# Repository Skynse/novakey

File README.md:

# NovaKey

An open-source 16-key macropad with three rotary encoders, custom firmware, and a companion configuration app.

## Novakey studio

Studio is the desktop app for the novakey. It can be used to configure profiles and keybinds

## Hardware

The PCB was designed in KiCad. Source files are in `kicad_files/`.

<table>
  <tr>
    <td align="center"><br><sub>Top</sub></td>
    <td align="center"><br><sub>Bottom</sub></td>
  </tr>
</table>

<details>
<summary>Schematic</summary>

</details>

## Bill of materials

### Electronics

| Ref | Qty | Part | Footprint / notes |
| --- | --- | --- | --- |
| A1 | 1 | Raspberry Pi Pico | Through-hole ([datasheet](https://datasheets.raspberrypi.com/pico/pico-datasheet.pdf)) |
| U2 | 1 | 0.91" 128x32 I2C OLED (ER-OLEDM0.91-1) | I2C ([datasheet](https://www.buydisplay.com/download/manual/ER-OLEDM0.91-1_Datasheet.pdf)) |
| SW1–SW3 | 3 | EC11 rotary encoder with push switch | Alps EC11E, vertical, 20 mm shaft |
| SW4–SW19 | 16 | Kailh MX hotswap socket | MX 1.00u |
| D1–D16 | 16 | Signal diode (e.g. 1N4148) | DO-35 through-hole, 7.62 mm pitch |
| — | 1 | NovaKey PCB | Gerbers in `pcbway_production/` |

### Mechanical

| Qty | Part | Source |
| --- | --- | --- |
| 16 | MX-style switches | Any MX-compatible switch |
| 16 | 1u keycaps | Any MX-compatible keycaps |
| 3 | Encoder knobs | 3D printed, `CAD/Knob.FCStd` |
| 1 | Enclosure base | 3D printed, `CAD/enclosure_v3/Base_flat.stl` |
| 1 | Enclosure top | 3D printed, `CAD/enclosure_v3/Upper_flat_base.stl` |

The KiCad-exported BOM is in `kicad_files/bill_of_materials.csv`.

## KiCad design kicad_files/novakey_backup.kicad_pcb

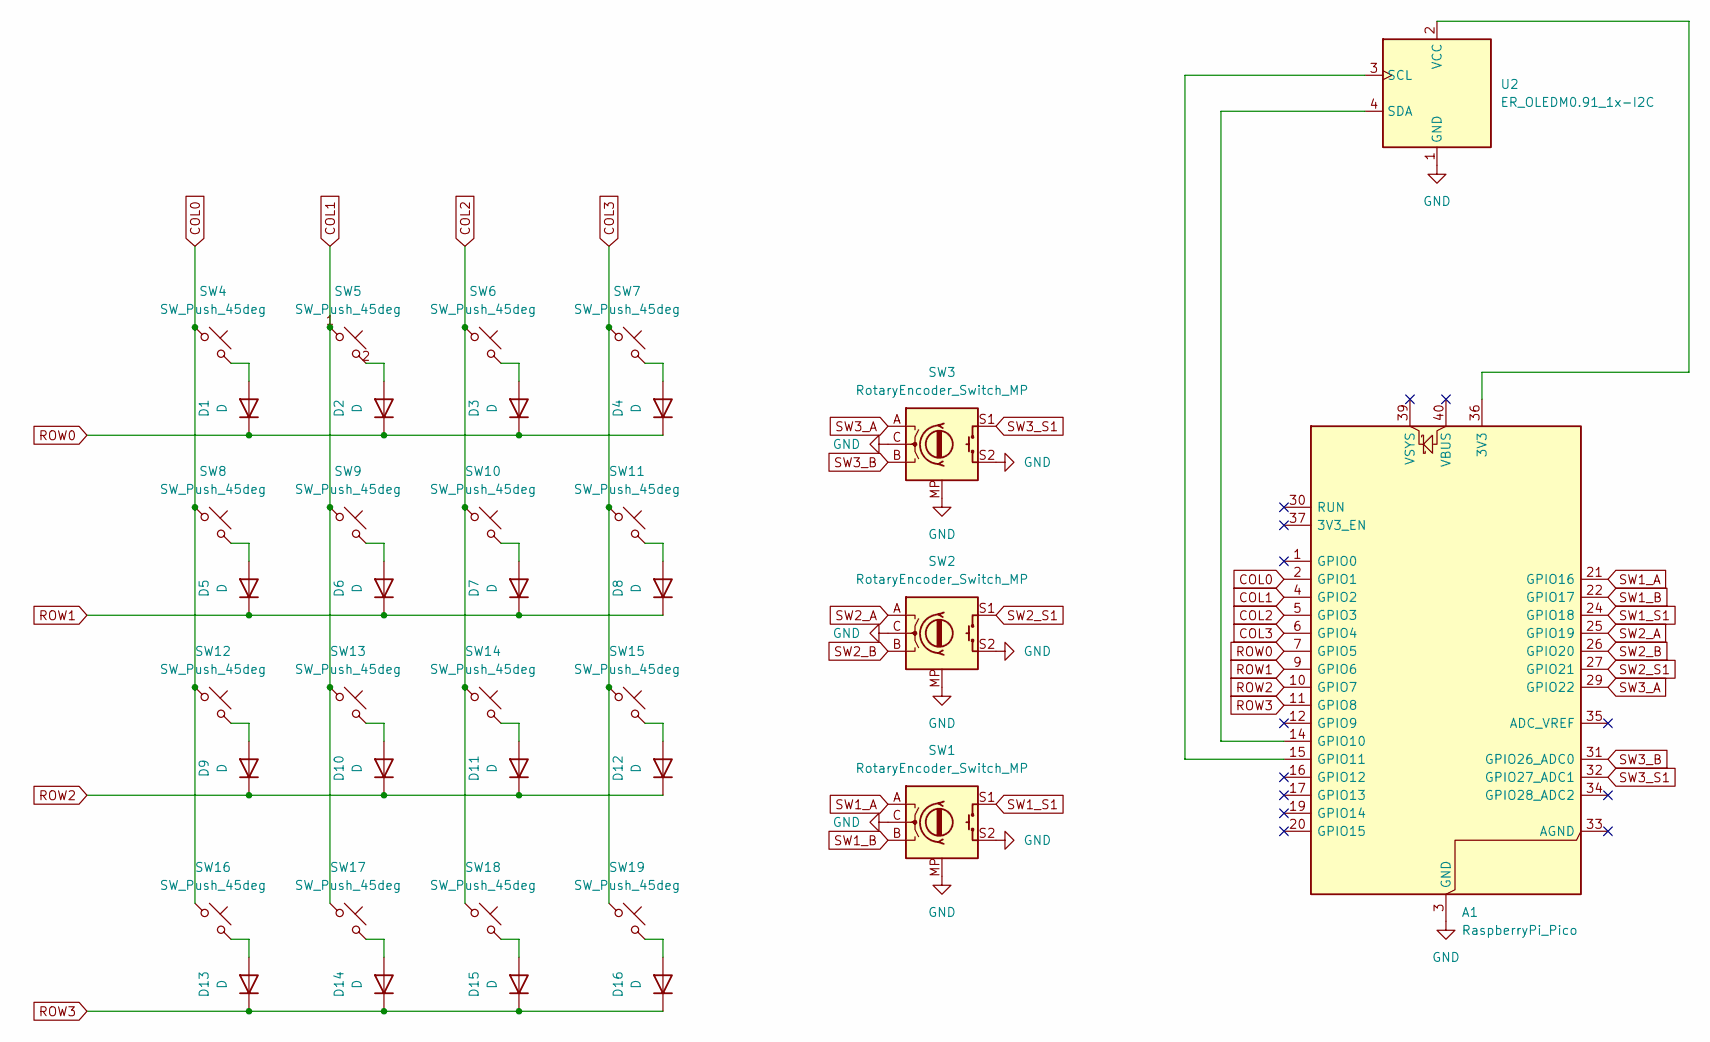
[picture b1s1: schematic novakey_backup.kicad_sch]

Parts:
A1: RaspberryPi_Pico; RaspberryPi_Pico_Common_THT
D1, D2, D3, D4, D5, D6, D7, D8, D9, D10, D11, D12, D13, D14, D15, D16: D; D_DO-35_SOD27_P7.62mm_Horizontal
SW1, SW2, SW3: RotaryEncoder_Switch_MP; RotaryEncoder_Alps_EC11E-Switch_Vertical_H20mm
SW4, SW5, SW6, SW7, SW8, SW9, SW10, SW11, SW12, SW13, SW14, SW15, SW16, SW17, SW18, SW19: SW_Push_45deg; SW_Hotswap_Kailh_MX_1.00u
U2: ER_OLEDM0.91_1x-I2C

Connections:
COL0: A1.2 (GPIO1), SW4.1, SW8.1, SW12.1, SW16.1
COL1: A1.4 (GPIO2), SW5.1, SW9.1, SW13.1, SW17.1
COL2: A1.5 (GPIO3), SW6.1, SW10.1, SW14.1, SW18.1
COL3: A1.6 (GPIO4), SW7.1, SW11.1, SW15.1, SW19.1
GND: A1.3 (GND), A1.8 (GND), A1.13 (GND), A1.18 (GND), A1.23 (GND), A1.28 (GND), A1.38 (GND), SW1.C, SW1.MP, SW1.S2, SW2.C, SW2.MP, SW2.S2, SW3.C, SW3.MP, SW3.S2, U2.1 (GND)
unnamed: A1.36 (3V3), U2.2 (VCC)
unnamed: A1.14 (GPIO10), U2.4 (SDA)
unnamed: A1.15 (GPIO11), U2.3 (SCL)
unnamed: D1.2 (A), SW4.2
unnamed: D2.2 (A), SW5.2
unnamed: D3.2 (A), SW6.2
unnamed: D4.2 (A), SW7.2
unnamed: D5.2 (A), SW8.2
unnamed: D6.2 (A), SW9.2
unnamed: D7.2 (A), SW10.2
unnamed: D8.2 (A), SW11.2
unnamed: D9.2 (A), SW12.2
unnamed: D10.2 (A), SW13.2
unnamed: D11.2 (A), SW14.2
unnamed: D12.2 (A), SW15.2
unnamed: D13.2 (A), SW16.2
unnamed: D14.2 (A), SW17.2
unnamed: D15.2 (A), SW18.2
unnamed: D16.2 (A), SW19.2
ROW0: A1.7 (GPIO5), D1.1 (K), D2.1 (K), D3.1 (K), D4.1 (K)
ROW1: A1.9 (GPIO6), D5.1 (K), D6.1 (K), D7.1 (K), D8.1 (K)
ROW2: A1.10 (GPIO7), D9.1 (K), D10.1 (K), D11.1 (K), D12.1 (K)
ROW3: A1.11 (GPIO8), D13.1 (K), D14.1 (K), D15.1 (K), D16.1 (K)
SW1_A: A1.21 (GPIO16), SW1.A
SW1_B: A1.22 (GPIO17), SW1.B
SW1_S1: A1.24 (GPIO18), SW1.S1
SW2_A: A1.25 (GPIO19), SW2.A
SW2_B: A1.26 (GPIO20), SW2.B
SW2_S1: A1.27 (GPIO21), SW2.S1
SW3_A: A1.29 (GPIO22), SW3.A
SW3_B: A1.31 (GPIO26_ADC0), SW3.B
SW3_S1: A1.32 (GPIO27_ADC1), SW3.S1

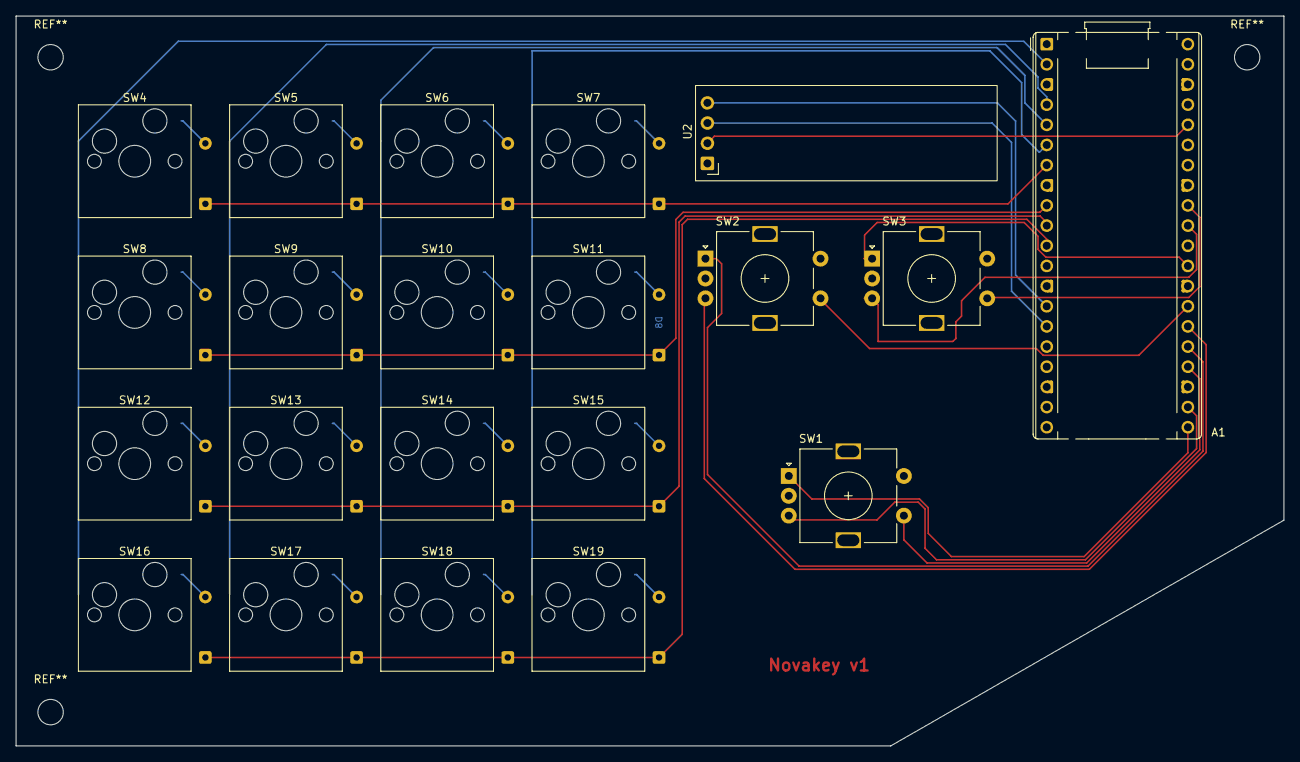
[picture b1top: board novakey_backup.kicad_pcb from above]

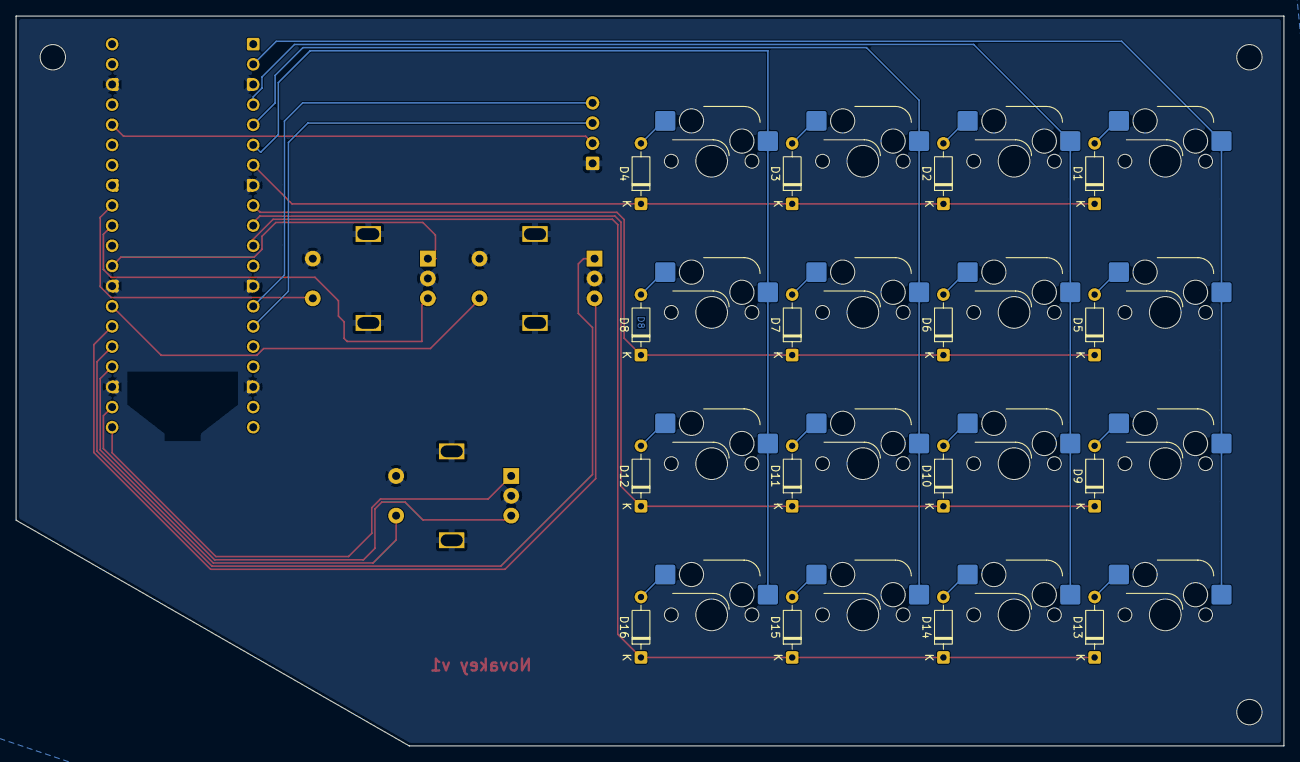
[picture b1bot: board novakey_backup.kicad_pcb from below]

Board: 2 copper layers, 159.7 x 91.9 mm, 37 parts (16 on the bottom side), 37 nets.

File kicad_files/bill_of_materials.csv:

"Reference","Qty","Value","DNP","Exclude from BOM","Exclude from Board","Footprint","Datasheet"
"A1","1","RaspberryPi_Pico","","","","Module:RaspberryPi_Pico_Common_THT","https://datasheets.raspberrypi.com/pico/pico-datasheet.pdf"
"D1,D2,D3,D4,D5,D6,D7,D8,D9,D10,D11,D12,D13,D14,D15,D16","16","D","","","","Diode_THT:D_DO-35_SOD27_P7.62mm_Horizontal",""
"SW1,SW2,SW3","3","RotaryEncoder_Switch_MP","","","","Rotary_Encoder:RotaryEncoder_Alps_EC11E-Switch_Vertical_H20mm",""
"SW4,SW5,SW6,SW7,SW8,SW9,SW10,SW11,SW12,SW13,SW14,SW15,SW16,SW17,SW18,SW19","16","SW_Push_45deg","","","","PCM_Switch_Keyboard_Hotswap_Kailh:SW_Hotswap_Kailh_MX_1.00u",""
"U2","1","ER_OLEDM0.91_1x-I2C","","","","Display:ER_OLEDM0.91_1x-I2C","https://www.buydisplay.com/download/manual/ER-OLEDM0.91-1_Da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"
